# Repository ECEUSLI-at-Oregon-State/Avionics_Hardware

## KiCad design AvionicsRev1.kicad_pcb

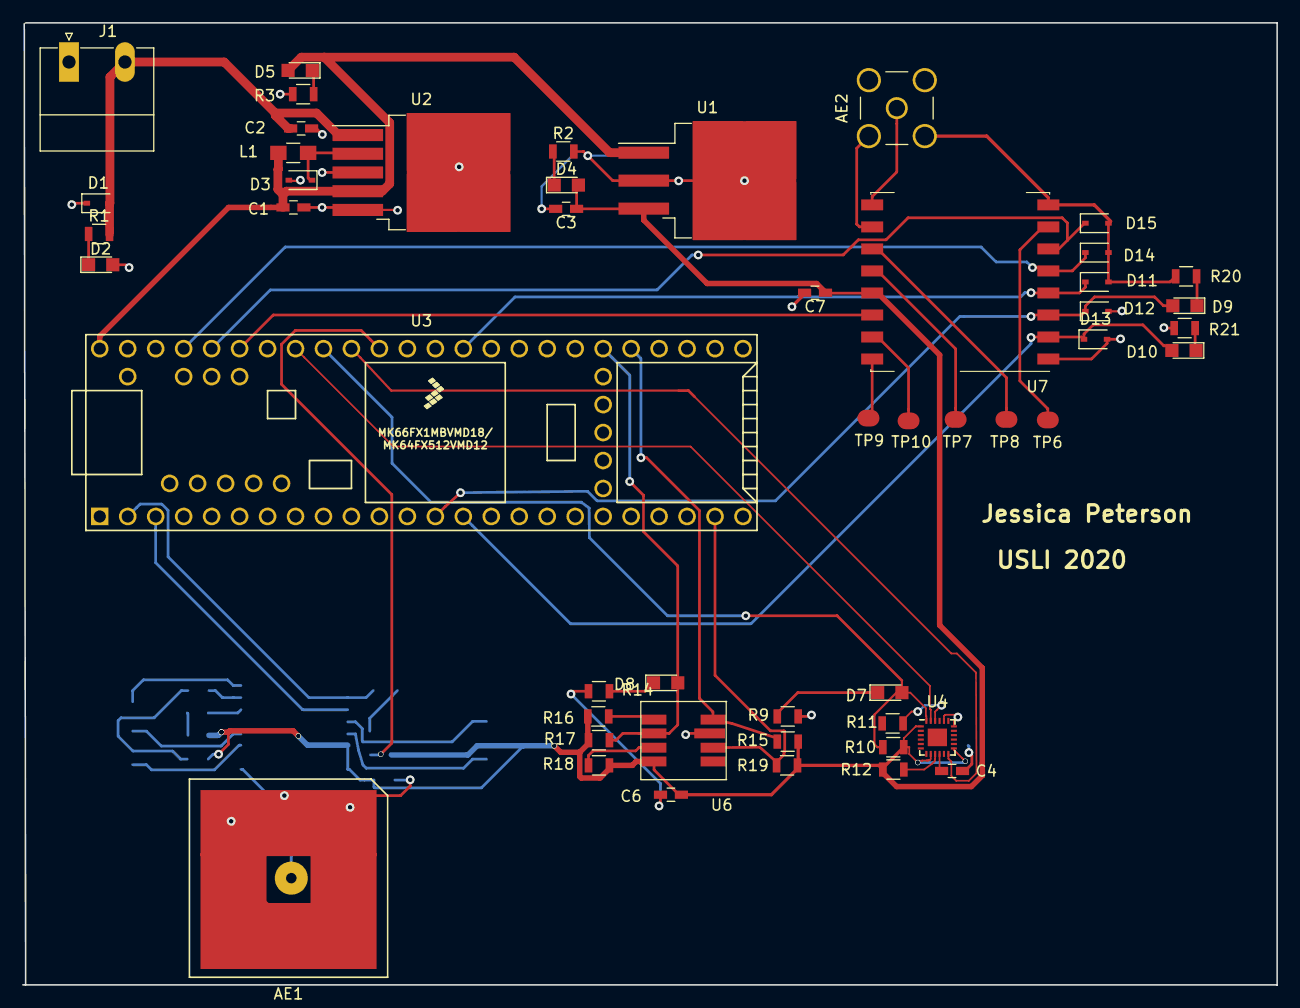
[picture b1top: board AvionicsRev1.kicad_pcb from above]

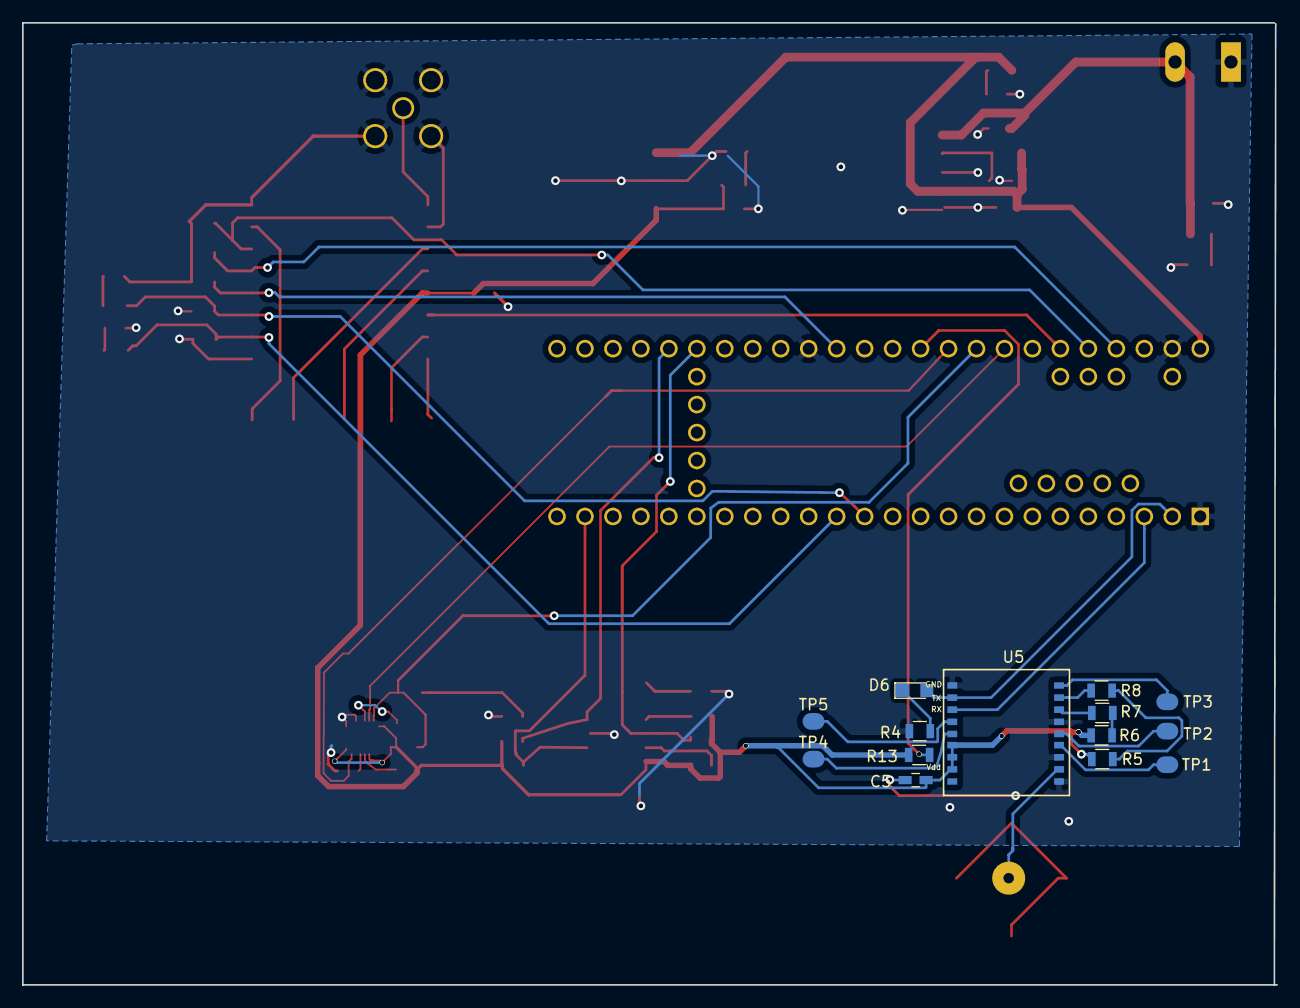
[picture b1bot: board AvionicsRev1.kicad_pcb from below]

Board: 2 copper layers, 113.9 x 87.4 mm, 64 parts (14 on the bottom side), 49 nets.

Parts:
AE1: Antenna_Shield; GPS-antenna
AE2: Antenna_Shield; SMA_THT_Jack_Straight
C1: 0.47u; C_0603_HandSoldering
C2: C; C_0603_HandSoldering
C3: 33u; C_0603_HandSoldering
C4, C5, C6, C7: 0.1u; C_0603_HandSoldering
D1: D; D_SOD-323
D2, D4, D5, D6, D7, D8, D9, D10: LED; LED_0805
D3: D_Schottky; D_SOD-323
D11, D12, D13, D14, D15: D_Zener; D_SOD-323
J1: Conn_01x02_Male; PhoenixContact_MC-G_02x5.08mm_Angled
L1: L; L_0805_HandSoldering
R1: 1K; R_0805
R2, R3, R4, R9, R14, R20, R21: 500; R_0805
R5, R6, R13: R_US; R_0805
R7, R8, R11: 22; R_0805
R10, R12, R15, R16, R17: 2.2K; R_0805
R18, R19: 10K; R_0805
TP1, TP2, TP3, TP4, TP5, TP6, TP7, TP8, TP9, TP10: TestPoint
U1: LM3940; TO-263-3_TabPin2
U2: LM2576HVS-5; TO-263-5_TabPin3
U3: Teensy_3.6; Teensy35_36
U4: MPU-9250; QFN-24-1EP_3x3mm_Pitch0.4mm
U5: MAX_M8; MAX-M8Q
U6: MS5803-14BA
U7: RFM95W-915S2; Hopref_RFM9XW_SMD

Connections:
+3V3: C3.1, C5.2, C6.1, C7.1, D4.2, R5.1, R6.1, R10.2, R12.2, R13.1, R15.1, R16.2, R17.1, R18.2, R19.1, U1.3, U4.1, U4.8, U4.13, U5.6, U5.7, U5.8, U6.5, U7.13
+5V: C1.1, D5.2, L1.2, U1.1, U2.4, U3.42
+12V: C2.1, D1.2, J1.2, R1.2, U2.1
BaromPress_CS: R19.2, U3.31, U6.3
BaromPress_SCL: R15.2, U3.37, U6.1
BaromPress_SDA: D8.2, R17.2, U3.38, U6.7
GND: AE1.2, AE2.2, C1.2, C2.2, C3.2, C4.2, C5.1, C6.2, C7.2, D1.1, D2.2, D3.2, D11.2, D12.2, D13.2, D14.2, D15.2, J1.1, R2.2, R3.2, R4.2, R9.2, R14.2, R20.2, R21.2, U1.2, U2.3, U2.5, U3.40, U3.43, U3.45, U4.18, U4.20, U5.1, U5.10, U5.12, U5.15, U6.2, U7.1, U7.8, U7.10
GPS_RESETN: R13.2, U3.16
GPS_RXD: U3.1, U5.3
GPS_SCL: R5.2, R8.2
GPS_SDA: R6.2, R7.2
GPS_TXD: D6.2, U3.0, U5.2
IMU_INT: U3.17, U4.12
IMU_SCL: U3.19, U4.23
IMU_SDA: D7.2, R10.1, U3.18, U4.24
unnamed: AE1.1, U5.11
unnamed: AE2.1, U7.9
unnamed: C4.1, U4.10
unnamed: D2.1, R1.1
unnamed: D3.1, L1.1, U2.2
unnamed: D4.1, R2.1
unnamed: D5.1, R3.1
unnamed: D6.1, R4.1
unnamed: D7.1, R9.1
unnamed: D8.1, R14.1
unnamed: D9.1, R20.1
unnamed: D10.1, R21.1
unnamed: R7.1, U5.16
unnamed: R8.1, U5.17
unnamed: R11.2, U4.22
unnamed: R12.1, U4.9
unnamed: R16.1, U6.8
unnamed: R18.1, U6.6
unnamed: TP1.1, U5.13
unnamed: TP2.1, U5.14
unnamed: TP3.1, U5.18
unnamed: TP4.1, U5.5
unnamed: TP5.1, U5.4
unnamed: TP6.1, U7.7
unnamed: TP7.1, U7.12
unnamed: TP8.1, U7.11
unnamed: TP9.1, U7.16
unnamed: TP10.1, U7.15
Transceiver_CS: D14.1, U3.23, U7.5
Transceiver_IRQ: U3.21, U7.14
Transceiver_MISO: D10.2, D13.1, U3.12, U7.2
Transceiver_MOSI: D9.2, D12.1, U3.11, U7.3
Transceiver_RST: D15.1, U3.22, U7.6
Transceiver_SCK: D11.1, U3.13, U7.4

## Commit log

2019-11-23 The first board sent to FAB
2019-11-23 The Arduino Code for the first subscale
2019-12-05 Code subscale1
